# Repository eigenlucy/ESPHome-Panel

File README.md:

# izzymonitor
<a href="https://eigenlucy.github.io/projects/izzymonitor">esp32-s3 based home assistant control panel</a>

<a href="https://github.com/izzyhub/izzymonitor-firmware">Rust firmware development repo</a> (thanks izzy!)

# Downloading Gerbers/PCBA files for assembly service
PCBA files are generated in the build artifacts on each commit. Download the build artifacts from the latest commit under the Actions tab. Upload the default gerber zip to JLCPCB, and use default.csv for the BOM file + default.pos.csv for the CPL file

# Requirements 
<li><a href="https://docs.atopile.io/latest/">atopile</a></li>
<li><a href="https://rustup.rs/">rust</a>, <a href="https://docs.esp-rs.org/book/installation/riscv-and-xtensa.html">espup</a>, <a href="https://github.com/esp-rs/espflash">espflash</a></li>

# Directory
## Ato builds
<li>Ato builds listed in ato.yaml</li>
<li>Veramonitor.ato is the main build. The final PCB is build from this, and the corresponding kicad project is in elec/layouts/default/veramonitor.kicad_pro</li>
<li>kailh-sw.ato contains the keyswitch+neopixel module. kicad files are located in elec/layouts/kailh-sw</li>
<li>MAX98357AETE_plus_T.ato contains the ClassDAmp module</li>

# TESTING IN PROGRESS:
## <a href="https://www.waveshare.com/wiki/1.8inch_LCD_Module">Wavshare 1.8in LCD Module</a> with <a href="https://crates.io/crates/st7735-lcd">ST7735 Controller</a>
module TFTDisplay in elec/src _1_peroid_8INCH_space_MODULE.ato
<a href="https://jlcpcb.com/partdetail/Waveshare-1_8inch_LCDModule/C359940">LCSC_ID = C359940</a>

SPI Pin mapping (elec/src/veramonitor.ato, line 67):
```
    lcd.spi.mosi ~ micro.io13; lcd.spi.sck ~ micro.io12; lcd.spi.cs ~ micro.io11; lcd.spi.dc ~ micro.io10; lcd.spi.reset ~ micro.io9; lcd.spi.backlightEN ~ micro.io46
```

##  <a href="https://learn.adafruit.com/adafruit-max98357-i2s-class-d-mono-amp/overview">MAX98357</a> Amp + Speaker  
Uses <a href="https://learn.adafruit.com/adafruit-max98357-i2s-class-d-mono-amp/overview">MAX98357</a> (LCSC ID = <a href="https://jlcpcb.com/partdetail/978950-MAX98357AETET/C910544">C910544</a>) 3W Class D amplifier IC + KLJ-1304T Speaker (LCSC_ID = C18186315). ESP32-S3 sends digital audio data to MAX98357 via I2S.

I2S Pin Mapping (veramonitor.ato, line 73):
```
    amp.LRCLK ~ micro.io8; amp.BCLK ~ micro.io18; amp.DIN ~ micro.io17
```
## Test <a href="https://jlcpcb.com/partdetail/OPSCOOptoelectronics-SK6805EC20/C2890036">SK6805 neopixels</a>
WS2812B style protocol. Defined in elec/src/sk6805-ec20/elec/src/sk6805-ec20.ato

Neopixels invoked and configured in each KailhSW module

Neopixel Pin Maping (veramonitor.ato, line 70):
```
    micro.io16 ~ sw1.DIN; sw1.DOUT ~ sw2.DIN; sw2.DOUT ~ sw3.DIN; sw3.DOUT ~ sw4.DIN; sw4.DOUT ~ sw5.DIN; sw5.DOUT ~ sw6.DIN
```
## <a href="https://jlcpcb.com/partdetail/Kailh-CPG1511F01S05/C400225">CPG1511F01S05</a> Kailh Switches
Accomodates standard keycaps
<a href="https://jlcpcb.com/parts/componentSearch?searchTxt=C400225">LCSC_ID: C400225</a> Kail module configured in elec/src/kailh-sw.ato.

Active low. Pin mappings:
```
    micro.io14 ~ sw1.KEY; micro.io21 ~ sw2.KEY; micro.io47 ~ sw3.KEY; micro.io48 ~ sw4.KEY; micro.io45 ~ sw5.KEY; micro.io35 ~ sw6.KEY
```
SW1 ~ GPIO14; SW2 ~ GPIO21; SW3 ~ GPIO47; SW4 ~ GPIO48; GPIO45 ~ SW5; SW6 ~ GPIO35

## <a href="https://www.digikey.com/en/products/detail/knowles/SPH0641LU4H-1/5332438">SPH0641LU4h1</a> MEMS microphone
<a href="https://jlcpcb.com/partdetail/Knowles-SPH0641LU4H1/C2879853">LCSC_ID = C2879853</a>

PDM Pin Mappings:
```
    pdm.pdm_sel ~ mic.SELECT; pdm.pdm_sel ~ micro.io3
    pdm.pdm_clk ~ mic.CLOCK; pdm.pdm_clk ~ micro.io5
    pdm.pdm_data ~ mic.DATA; pdm.pdm_data ~ micro.io4
```

# To Do 
## 1: Verify basic functionality
## 2: Finish rust firmware
## 3: Home assistant integration
## 4: 3D printed enclosure/wall panel mount

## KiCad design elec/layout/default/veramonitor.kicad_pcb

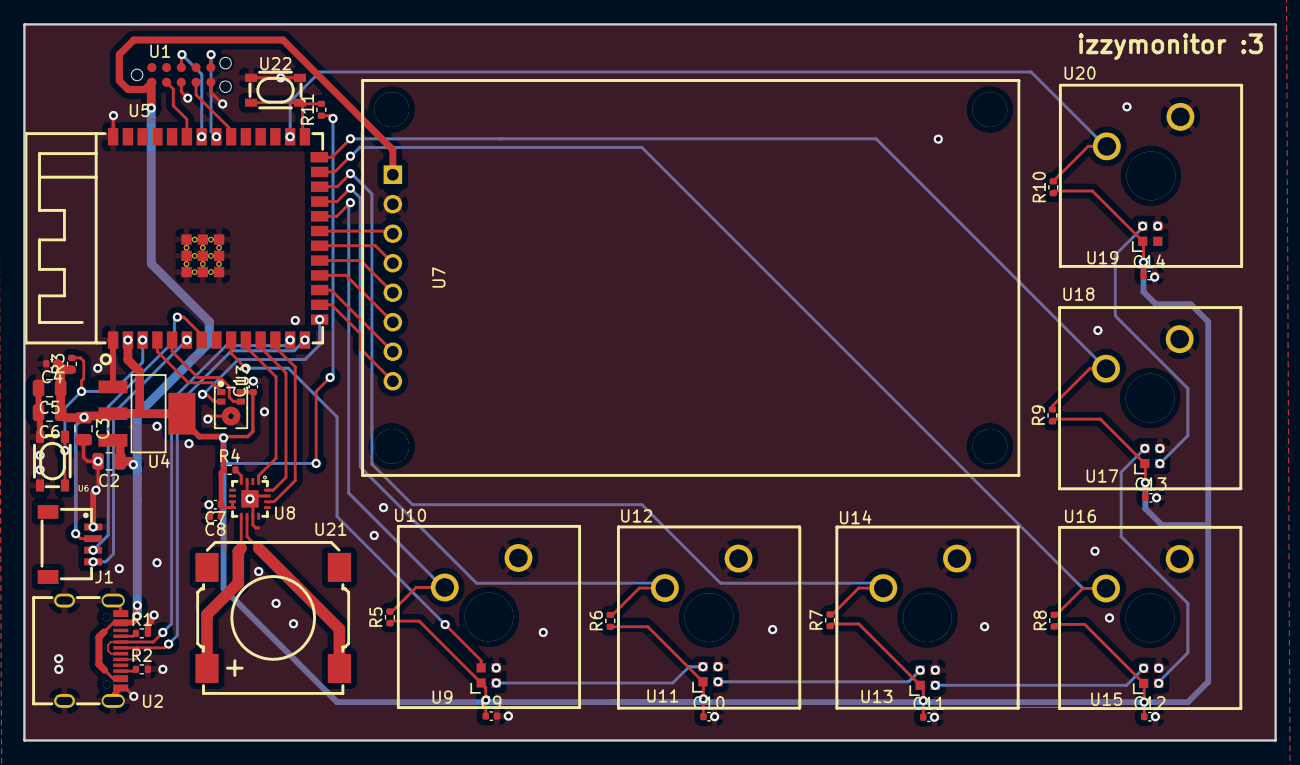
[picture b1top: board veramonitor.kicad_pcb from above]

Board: 2 copper layers, 107.7 x 61.6 mm, 48 parts (0 on the bottom side), 44 nets.

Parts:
C1: 50V 10nF X7R ±10% 0402 Multilayer Ceramic Capacit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; C0402
C2, C3, C5, C6: 25V 10uF X5R ±10% 0805 Multilayer Ceramic Capacit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; C0805
C4, C8, C9, C10, C11, C12, C13, C14: 16V 100nF X7R ±10% 0402 Multilayer Ceramic Capaci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; C0402
C7: 6.3V 10uF X5R ±20% 0402 Multilayer Ceramic Capaci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; C0402
J1: ?; CONN-SMD_4P-P1.00_SM04B-SRSS-TB-LF-SN
R1, R2: 62.5mW Thick Film Resistors 50V ±100ppm/℃ ±1% 4.7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; R0402
R3, R4, R5, R6, R7, R8, R9, R10, R11: 62.5mW Thick Film Resistors 50V ±100ppm/℃ ±1% 10k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; R0402
U1: ?; TAG-CONNECT_TC2050-IDC
U2: ?; USB-C-SMD_KH-TYPE-C-16P
U3: ?; MIC-SMD_5P_L3.5-W2.7-P0.82_SPH0641LU4H-1
U4: ?; SOT-223-3_L6.5-W3.4-P2.30-LS7.0-BR
U5: ?; WIRELM-SMD_ESP32-S3-WROOM-1
U6, U22: ?; KEY-SMD_4P-L4.2-W3.2-P2.20-LS4.6
U7: ?; LCD-TH_L56.5-W34.0_1-8INCH-LCD-MODULE
U8: ?; TQFN-16_L3.0-W3.0-P0.50-BL-EP1.5
U9, U11, U13, U15, U17, U19: ?; LED-SMD_4P-L2.0-W2.0-BR
U10, U12, U14, U16, U18, U20: ?; KEY-TH_CPG1511F01S0X
U21: ?; BUZ-SMD_4P-L13.0-W13.0-P11.4-BL

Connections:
backlighten: U5.16, U7.8
bclk: U5.11, U8.16
cc1: R1.1, U2.A5
cc2: R2.1, U2.B5
cs: U5.19, U7.5
dc: U5.18, U7.6
din: U5.10, U8.1
dm: U2.A7, U2.B7, U5.13
dp: U2.A6, U2.B6, U5.14
dummy: U21.3, U21.4
en: R3.2, U5.3, U6.1, U6.2
gnd: C1.2, C2.2, C3.2, C4.2, C5.2, C6.2, C7.2, C8.2, C9.2, C10.2, C11.2, C12.2, C13.2, C14.2, J1.1, R1.2, R2.2, U1.3, U1.5, U2.1, U2.2, U2.3, U2.4, U2.A1, U2.A12, U2.B1, U2.B12, U3.3, U4.1, U5.1, U5.40, U5.41, U6.3, U6.4, U7.2, U8.3, U8.11, U8.15, U8.17, U9.3, U10.2, U11.3, U12.2, U13.3, U14.2, U15.3, U16.2, U17.3, U18.2, U19.3, U20.2, U22.3, U22.4
io14: R5.2, U5.22, U10.1
io16: U5.9, U9.4
io21: R6.2, U5.23, U12.1
io35: R10.2, U5.28, U20.1
io45: R9.2, U5.26, U18.1
io47: R7.2, U5.24, U14.1
io48: R8.2, U5.25, U16.1
lrclk: U5.12, U8.14
micro.ic-reset: U5.17, U7.7
micro.ic-vcc: R11.2, U5.27, U22.1, U22.2
mosi: U5.21, U7.3
n_period_c_period: U8.5, U8.6, U8.12, U8.13
outn: U8.10, U21.2
outp: U8.9, U21.1
pdm_clk: U3.4, U5.5
pdm_data: U3.1, U5.4
pdm_sel: U3.2, U5.15
sck: U5.20, U7.4
scl: J1.4, U5.6
sd_mode_hash: R4.2, U8.4
sda: J1.3, U5.7
sw1-dout: U9.2, U11.4
sw2-dout: U11.2, U13.4
sw3-dout: U13.2, U15.4
sw4-dout: U15.2, U17.4
sw5-dout: U17.2, U19.4
tck: U1.4, U5.32
tdi: U1.8, U5.34
tdo: U1.6, U5.33
tms: U1.2, U5.35
vcc: C2.1, U1.1, U2.A4, U2.A9, U2.B4, U2.B9, U4.3, U7.1
vcc-1: C1.1, C3.1, C4.1, C5.1, C6.1, C7.1, C8.1, C9.1, C10.1, C11.1, C12.1, C13.1, C14.1, J1.2, R3.1, R4.1, R5.1, R6.1, R7.1, R8.1, R9.1, R10.1, R11.1, U3.5, U4.2, U4.4, U5.2, U8.7, U8.8, U9.1, U11.1, U13.1, U15.1, U17.1, U19.1

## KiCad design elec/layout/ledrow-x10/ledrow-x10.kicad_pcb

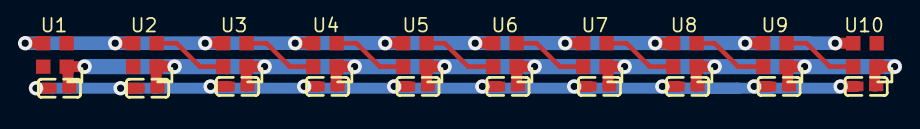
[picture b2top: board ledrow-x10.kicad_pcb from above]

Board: 2 copper layers, 20 parts (0 on the bottom side), 11 nets.

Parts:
C1, C2, C3, C4, C5, C6, C7, C8, C9, C10: 100nF ±10% 16V X7R; C0402-b3ef17
U1, U2, U3, U4, U5, U6, U7, U8, U9, U10: LED-SMD_4P-L2.0-W2.0-BR

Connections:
gnd: C1.2, C2.2, C3.2, C4.2, C5.2, C6.2, C7.2, C8.2, C9.2, C10.2, U1.3, U2.3, U3.3, U4.3, U5.3, U6.3, U7.3, U8.3, U9.3, U10.3
hv: C1.1, C2.1, C3.1, C4.1, C5.1, C6.1, C7.1, C8.1, C9.1, C10.1, U1.1, U2.1, U3.1, U4.1, U5.1, U6.1, U7.1, U8.1, U9.1, U10.1
io: U9.2, U10.4
io-1: U2.2, U3.4
io-2: U3.2, U4.4
io-3: U8.2, U9.4
vcc: U6.2, U7.4
vcc-1: U4.2, U5.4
vcc-2: U1.2, U2.4
vcc-3: U7.2, U8.4
vcc-4: U5.2, U6.4

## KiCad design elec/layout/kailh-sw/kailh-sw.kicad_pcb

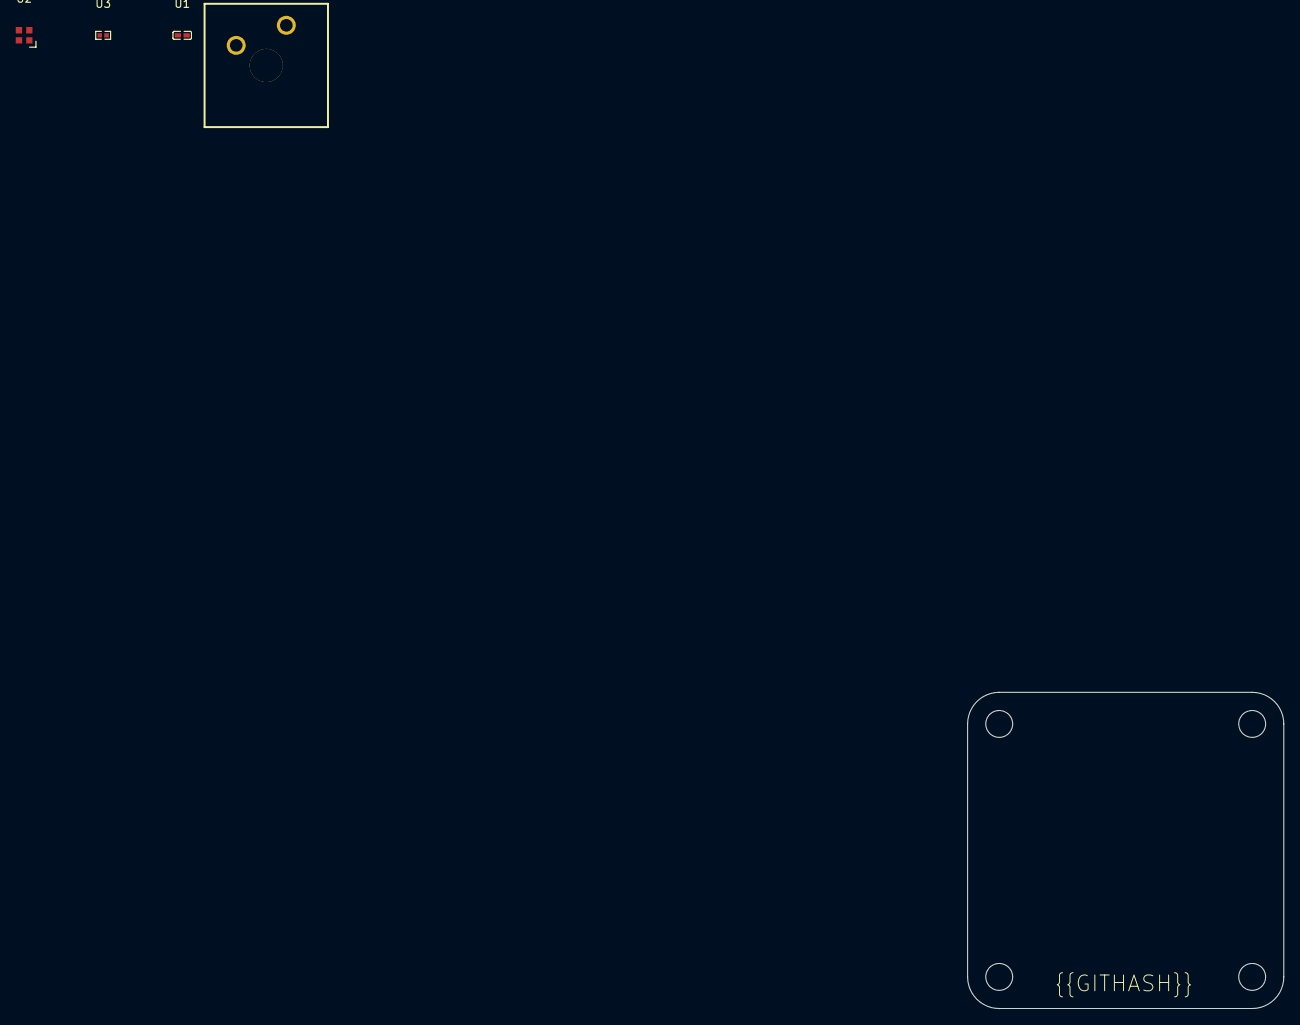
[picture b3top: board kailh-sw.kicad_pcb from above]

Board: 2 copper layers, 40.0 x 40.0 mm, 4 parts (0 on the bottom side), 3 nets, no tracks yet.

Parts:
U1: 100nF ±10% 16V X7R; C0402-b3ef17
U2: LED-SMD_4P-L2.0-W2.0-BR
U3: 10kΩ ±1% 62.5mW; R0402-56259e
U4: KEY-TH_CPG1511F01S0X

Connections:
KEY: U3.2, U4.1
gnd: U1.2, U2.3, U4.2
hv: U1.1, U2.1, U3.1

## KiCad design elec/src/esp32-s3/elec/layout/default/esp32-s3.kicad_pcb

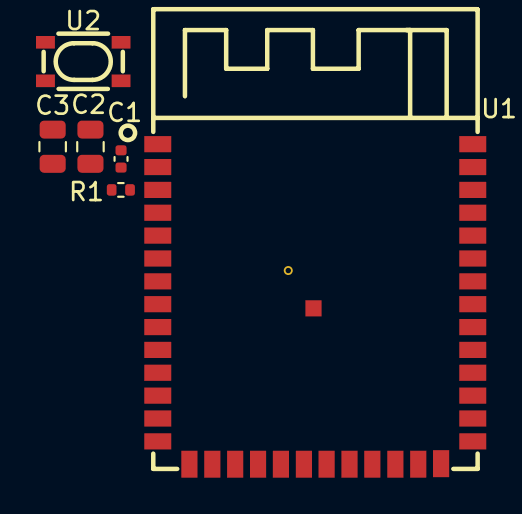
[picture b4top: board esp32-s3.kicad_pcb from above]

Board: 2 copper layers, 6 parts (0 on the bottom side), 3 nets, no tracks yet.

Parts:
C1: 16V 100nF X7R ±10% 0402 Multilayer Ceramic Capaci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; C0402
C2, C3: 25V 10uF X5R ±10% 0805 Multilayer Ceramic Capacit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; C0805
R1: 62.5mW Thick Film Resistors ±100ppm/℃ ±1% 10kΩ 04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; R0402
U1: WIRELM-SMD_ESP32-S3-WROOM-1
U2: KEY-SMD_4P-L4.2-W3.2-P2.20-LS4.6

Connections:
en: R1.2, U1.3, U2.1, U2.2
ic-gnd: C1.2, C2.2, C3.2, U1.1, U1.40, U1.41, U2.3, U2.4
vcc: C1.1, C2.1, C3.1, R1.1, U1.2

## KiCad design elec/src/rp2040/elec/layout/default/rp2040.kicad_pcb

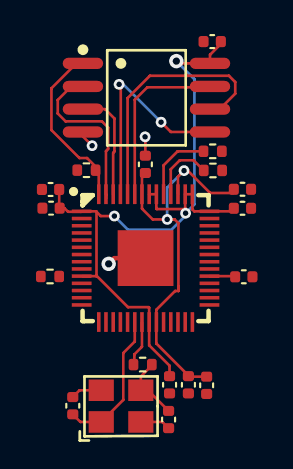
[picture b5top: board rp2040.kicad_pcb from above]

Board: 2 copper layers, 20 parts (0 on the bottom side), 15 nets.

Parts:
C1, C2: 50V 20pF C0G ±5% 0402 Multilayer Ceramic Capacito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; C0402
C3, C4, C5, C6, C7, C9, C10, C11: 16V 100nF X7R ±10% 0402 Multilayer Ceramic Capaci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; C0402
C8, C12: 25V 1uF X5R ±10% 0402 Multilayer Ceramic Capacito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; C0402
R1, R2: 62.5mW Thick Film Resistors ±100ppm/℃ ±1% 10kΩ 04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; R0402
R3: 62.5mW Thick Film Resistors ±100ppm/℃ ±1% 1kΩ 040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; R0402
R4, R5: 62.5mW Thick Film Resistors ±100ppm/℃ ±1% 27Ω 040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; R0402
U1: LQFN-56_L7.0-W7.0-P0.4-EP
U2: OSC-SMD_4P-L3.2-W2.5-BL
U3: SOIC-8_L5.3-W5.3-P1.27-LS8.0-BL

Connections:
cs-1: R2.2, U1.56, U3.1
gnd: C1.2, C2.2, C3.2, C4.2, C5.2, C6.2, C7.2, C8.2, C9.2, C10.2, C11.2, C12.2, U1.19, U1.57, U2.2, U2.4, U3.4
io0: U1.53, U3.5
io1: U1.55, U3.2
io2: U1.54, U3.3
io3: U1.51, U3.7
micro-vcc: C9.1, C10.1, C11.1, C12.1, U1.23, U1.45, U1.50
out: C2.1, R3.2, U2.3
run: R1.2, U1.26
sck-1: U1.52, U3.6
usb_dm: R5.2, U1.46
usb_dp: R4.1, U1.47
vcc: C3.1, C4.1, C5.1, C6.1, C7.1, C8.1, R1.1, R2.1, U1.1, U1.10, U1.22, U1.33, U1.42, U1.43, U1.44, U1.48, U1.49, U3.8
xin: C1.1, U1.20, U2.1
xout: R3.1, U1.21

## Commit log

2024-10-29 Configure project
2024-10-29 great success
2024-10-30 eod 10/30
2024-10-31 finished?
2024-10-31 finished maybe
2024-10-31 added fab outputs
2024-10-31 fixed errors
2024-10-31 new fab out
2024-11-01 probs done
2024-11-08 11/8
2024-11-11 fixed errors:
2024-11-11 order 2
2024-11-21 fixed usb-uart grounding
2024-12-15 removed usb-uart
2024-12-15 edits
2024-12-16 added keys
2024-12-16 checking DFM
2024-12-16 rerun
2025-01-30 readme checklist
2025-01-30 readme
2025-02-18 :woozy:
2025-02-18 editing layout
2025-02-26 IZZYMONITOR V2, FIXED SPACING AND ANT OVERHANG
